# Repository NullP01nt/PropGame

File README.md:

PropGame
========

Documentation, designs and source code for our Propeller-based Game Console.

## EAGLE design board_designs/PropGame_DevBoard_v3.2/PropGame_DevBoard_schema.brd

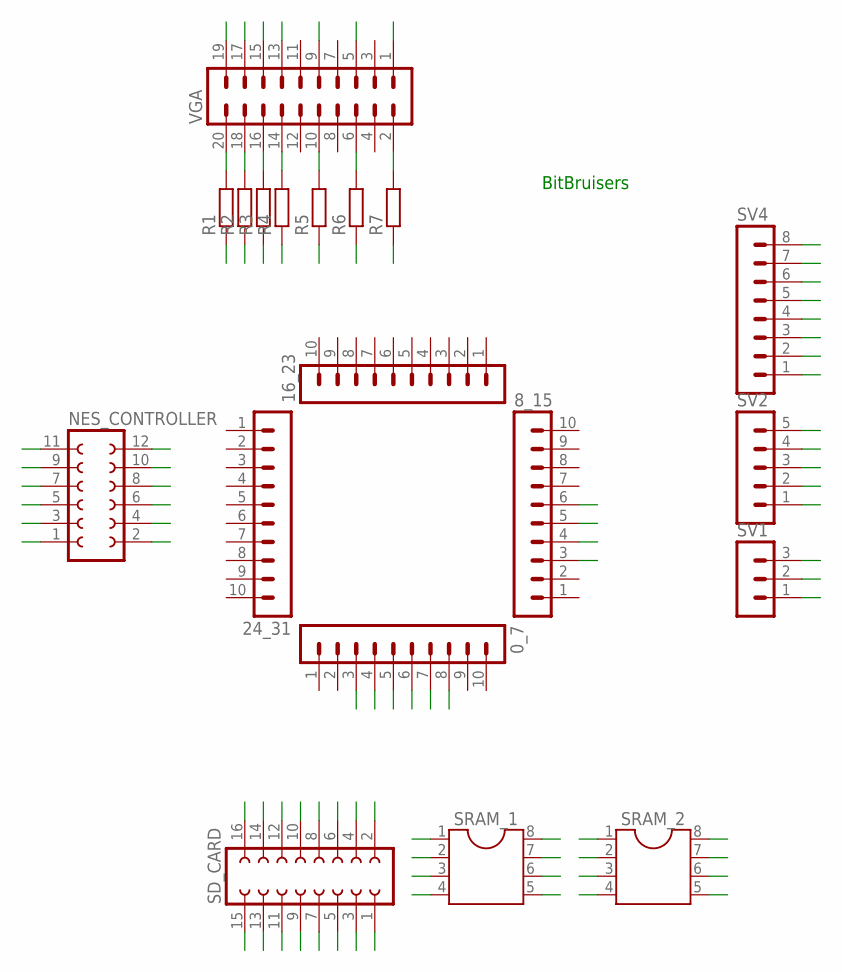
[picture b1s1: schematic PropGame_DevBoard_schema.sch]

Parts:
0_7, 8_15, 16_23, 24_31: MA10-1
NES_CONTROLLER: FE06-2
R1, R2, R3, R4, R5, R6, R7: R-EU_0204/7; 0204/7
SD_CARD: FE08-2
SRAM_1, SRAM_2: DIL8; DIL08
SV1: MA03-1
SV2: MA05-1
SV4: MA08-1
VGA: MA10-2

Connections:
3V3: SD_CARD.13, SD_CARD.14, SRAM_1.8, SRAM_2.8, SV1.1, SV1.2, SV1.3
5V: NES_CONTROLLER.3, NES_CONTROLLER.4, SD_CARD.11, SD_CARD.12, SV4.1, SV4.2, SV4.3
CLK: 8_15.3, NES_CONTROLLER.11, NES_CONTROLLER.12
CS_1: 0_7.6, SD_CARD.9, SD_CARD.10
CS_2: 0_7.7, SRAM_1.1
CS_3: 0_7.8, SRAM_2.1
DATA1: 8_15.5, NES_CONTROLLER.7, NES_CONTROLLER.8
DATA2: 8_15.6, NES_CONTROLLER.5, NES_CONTROLLER.6
GND: NES_CONTROLLER.1, NES_CONTROLLER.2, SD_CARD.1, SD_CARD.2, SD_CARD.15, SD_CARD.16, SRAM_1.4, SRAM_2.4, SV2.1, SV2.2, SV2.3, SV2.4, SV2.5, SV4.4, SV4.5, SV4.6, SV4.7, SV4.8
LATCH: 8_15.4, NES_CONTROLLER.9, NES_CONTROLLER.10
MISO: 0_7.5, SD_CARD.3, SD_CARD.4, SRAM_1.2, SRAM_2.2
MOSI: 0_7.4, SD_CARD.7, SD_CARD.8, SRAM_1.5, SRAM_2.5
unnamed: R1.2, VGA.20
unnamed: R2.2, VGA.18
unnamed: R3.2, VGA.16
unnamed: R4.2, VGA.14
unnamed: R5.2, VGA.10
unnamed: R6.2, VGA.6
unnamed: R7.2, VGA.2
SCK: 0_7.3, SD_CARD.5, SD_CARD.6, SRAM_1.6, SRAM_2.6
W_1: R1.1, VGA.19
W_2: R2.1, VGA.17
W_3: R3.1, VGA.15
W_4: R4.1, VGA.13
W_5: R5.1, VGA.9
W_6: R6.1, VGA.5
W_7: R7.1, VGA.1

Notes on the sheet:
BitBruisers

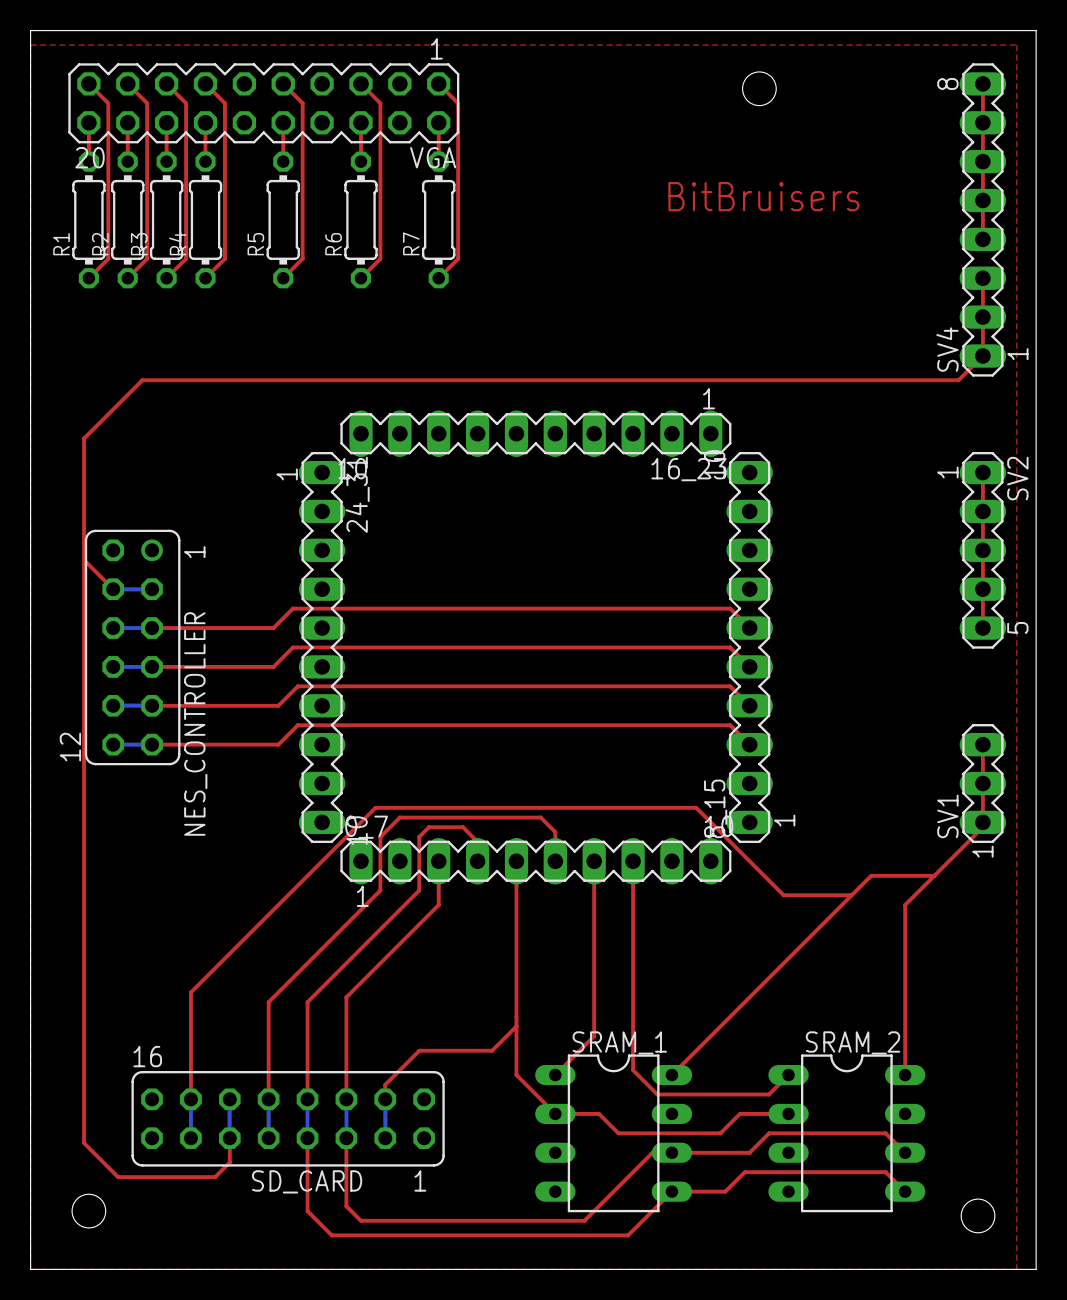
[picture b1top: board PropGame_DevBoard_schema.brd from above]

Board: 2 copper layers, 65.7 x 81.0 mm, 19 parts (0 on the bottom side), 27 nets.

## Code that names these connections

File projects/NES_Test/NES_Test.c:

/**
 * @file NES_Test.c
 * This is the main NES_Test program start point.
 */

/**
 * Main program function.
 */

#include <stdio.h>
#include <stdlib.h>
#include <propeller.h>

// Pin numbers
#define CLOCK   4
#define LATCH   5
#define DATA1   6
#define DATA2   7
#define BITS    8

// Direction types
#define OUTPUT  1
#define INPUT   0

#define HIGH    1
#define LOW     0

// Button values
#define BTN_RIGHT   (1<<7)
#define BTN_LEFT    (1<<6)
#define BTN_DOWN    (1<<5)
#define BTN_UP      (1<<4)
#define BTN_START   (1<<3)
#define BTN_SELECT  (1<<2)
#define BTN_B       (1<<1)
#define BTN_A       (1<<0)

void pinSet(int,int);
unsigned char buttons(void);
void readButtons(void);
int init_gamepad(void);

unsigned char P1_BUTTONS;
unsigned char P2_BUTTONS;

void print_buttons(unsigned char);

int main()
{
    printf("Hello world!\n");
    init_gamepad();
    while(1) {
        readButtons();
        print_buttons(P1_BUTTONS);
        print_buttons(P2_BUTTONS);
/*        if(P1_BUTTONS & BTN_START) {
            printf("[P1] Start pressed!\n");
        } else if(P1_BUTTONS & BTN_SELECT) {
            printf("[P1] Select pressed!\n");
        } else if(P1_BUTTONS & BTN_A) {
            printf("[P1] A pressed!\n");
        } else if(P1_BUTTONS & BTN_B) {
            printf("[P1] B pressed!\n");
        } else if(P1_BUTTONS & BTN_UP) {
            printf("[P1] Up pressed!\n");
        } else if(P1_BUTTONS & BTN_DOWN) {
            printf("[P1] Down pressed!\n");
        } else if(P1_BUTTONS & BTN_LEFT) {
            printf("[P1] Left pressed!\n");
        } else if(P1_BUTTONS & BTN_RIGHT) {
            printf("[P1] Right pressed!\n");
        }

        if(P2_BUTTONS & BTN_START) {
            printf("[P2] Start pressed!\n");
        } else if(P2_BUTTONS & BTN_SELECT) {
            printf("[P2] Select pressed!\n");
        } else if(P2_BUTTONS & BTN_A) {
            printf("[P2] A pressed!\n");
        } else if(P2_BUTTONS & BTN_B) {
            printf("[P2] B pressed!\n");
        } else if(P2_BUTTONS & BTN_UP) {
            printf("[P2] Up pressed!\n");
        } else if(P2_BUTTONS & BTN_DOWN) {
            printf("[P2] Down pressed!\n");
        } else if(P2_BUTTONS & BTN_LEFT) {
            printf("[P2] Left pressed!\n");
        } else if(P2_BUTTONS & BTN_RIGHT) {
            printf("[P2] Right pressed!\n");
        }*/
//        printf("0x%X\n",P1_BUTTONS);
        waitcnt(CLKFREQ/2+CNT);
    }
    return 0;
}

int init_gamepad()
{
    DIRA &= ~((1<<DATA1)|(1<<DATA2));   // DATA1 en DATA2 is INPUT
    DIRA |= ((1<<CLOCK)|(1<<LATCH));    // CLOCK en LATCH is OUTPUT

    pinSet(LATCH, HIGH);
    unsigned char tmp;
    tmp = buttons();
    if (tmp == 0) { return -1;
    }
    printf("%X",tmp);
    return 0;
}

void print_buttons(unsigned char input) {
    int i=BITS;
    printf("RLDUSSBA\n");
    for(i=BITS;i>0;i--) {
        printf("%d",input&(1<<(i-1))?1:0);
    }
    printf("\n");
}

void readButtons() {
    int i=0;
    pinSet(LATCH,LOW);
    pinSet(CLOCK,LOW);
    uint8_t p1b=0,p2b=0;
    uint8_t i1=0,i2=0;
    for(i=BITS;i>0;i--) {
        i1 = (INA & (1<<DATA1)) ? 0 : 1;
        i2 = (INA & (1<<DATA2)) ? 0 : 1;
        p1b |= (i1<<(BITS-i));
        p2b |= (i2<<(BITS-i));
        pinSet(CLOCK,HIGH);
        waitcnt(500+CNT);
        pinSet(CLOCK,LOW);
    }
    P1_BUTTONS = p1b;
    P2_BUTTONS = p2b;
}

unsigned char buttons()
{
    int i=0;
    pinSet(LATCH, LOW);
    pinSet(CLOCK, LOW);
    unsigned char btns = 0;
    unsigned char InBit1 = 0;
    for (i = BITS; i > 0; i--) {
        InBit1 = (INA & (1<<DATA1)) ? 0 : 1;
        btns |= (InBit1<<(BITS-i));
        pinSet(CLOCK,HIGH);
        waitcnt(500+CNT);
        pinSet(CLOCK,LOW);
    }
    pinSet(LATCH,HIGH);
    return btns;
}

void pinSet(int pin, int value)
{
    uint32_t mask = 1 << pin;
    uint32_t data = (value & 1) << pin;
    OUTA = (OUTA & ~mask) | data;
}

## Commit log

2012-11-04 Added documentation URLs for the Propeller and Wii Classic controller
2012-11-04 Added a list for proposed games
2012-11-06 Added an SD Card tutorial for Propeller (In Spin, mind you)
2012-11-06 Added Protoboard documents
2012-11-06 Added SD pinout, renamed the Prop docs
2012-11-06 Added more documents
2012-11-06 Added some new urls, as well as a reference to a SD card lib
2012-11-17 Nice Propeller Cookbook.
2012-11-17 Added link to awesome webshop
2012-11-17 Added documentation regarding external SRAM for the Propeller
2012-11-18 Added a small list of things to get at Farnell as well as specs regarding FAT filesystems
2012-11-19 Added rudimentary partition table reading etc.
2012-11-19 Revised main.c in src/fat/
2012-11-19 Revised partition table stuff again
2012-11-19 Revised main.c and disk.c
2012-11-19 Fixed up main.c so we can load partition entries in a for loop
2012-11-19 Made output as given by the software a bit more readable
2012-11-20 Removed unused imports
2012-11-20 Revised Makefile, added clean as a 'phony' target
2012-11-20 Renamed 'fat' to 'disk' since it encompasses more than just the filesystem
2012-11-20 Started work on FAT interpretation, both FAT16 and FAT32?
2012-11-20 worked on output of dump_ebpb()
2012-11-20 Volume Record is now being properly read, from what I can tell
2012-11-20 Added the USE_FAT32 define again
2012-11-24 Removed disk files, added everything to fat.h and fat.c
2012-11-24 Revised naming for functions, structs etc.
2012-11-25 Revised gitignore to ignore *.swp files
2012-11-25 updated functions to new naming
2012-11-25 Added ignore rules for *.vim files (among others Sessions etc.)
2012-11-25 Seperated FAT16 and FAT32 code
2012-11-25 Fixed signed-ness issue with print_char_bytes
2012-11-25 Changed default file in main.c
2012-11-25 Added example code
2012-11-25 Re-indented example code in docs/FAT32
2012-11-30 Removed old FAT specs document, added new HTML based version. Revised FAT code
2012-12-16 Added blank files for various interfaces
2012-12-16 Added link to Eclipse plugin for PropGCC
2012-12-17 Files for testing with SPI
2012-12-17 Added documentation about SPI for the propeller
2012-12-17 modified files
2013-01-18 Added NES Gamepad project
2013-01-18 Begin NES controller
2013-01-18 Revised Gamepad code
2013-01-18 Added a board configuration stump, have to look at the cache driver
2013-01-18 Added several working folders
2013-01-20 Added full propgcc tar.gz for reference and demos
2013-01-21 Added sd loader stub
2013-01-21 Added Eagle files as well as VGA
2013-01-22 Working on revised makefile, removed sd_cache_loader.c in favour of sd_loader.c
2013-01-22 Added documentation and vgademo
2013-01-22 Added basics for a 'game' project in src/pad_tester
2013-01-22 Added begin for testgame
2013-01-22 Completed gamepad functions, added some pin functions
2013-01-22 Removed built binary files
2013-01-22 Some minor changes, add's and removes
2013-01-22 pad_tester project compiles with Makefile
2013-01-22 revised gamepad.c to allow for SinglePlayer and MultiPlayer definitions
2013-01-22 Removed some stuff, useless
2013-01-22 tags
2013-01-22 Reduced NesGamepad_2 to NesGamepad
2013-01-22 Renamed NesGamepad_2{.c|.side} to NesGamepad{.c|.side}
2013-01-22 added second demo
2013-01-22 Added an include to gamepad.c for standard data sizes
2013-01-22 Added a run target to pad_tester's Makefile
2013-01-23 Started work on segloader, moved gameblade.cfg to pad_tester/
2013-01-23 Added board design and begin snake game
2013-01-23 Added a run target for segloader, modified file I/O slightly, filtering by extension is possible
2013-01-23 Cleaned up the repository
2013-01-23 Added the board config and gamepad code to the segloader directory
2013-01-23 Added doc about VGA and new project for incl vga and game
2013-01-23 Added some more things related to the gamepad code, I missed pins.{c|h} and a reference to PAD_ONE
2013-01-23 Another doc about VGA, this one for the propeller
2013-01-23 Revised vgademo, added a run target to the Makefile, added the board config to the directory, removed a pre-built binary
2013-01-23 Attempt to integrate VGA into SegLoader, non-funct
2013-01-23 Removed all VGA code from SegLoader
2013-01-23 Added common base for makefiles, added text mode VGA to SegLoader, which seems to work
2013-01-23 Revised gitignore so it doesn't list elf files or out files
2013-01-23 Working on SegLoader, has rudimentary controller working
2013-01-23 New board design and added projects for game
2013-01-23 Revised File I/O, it makes an array of 24 file entries and displays them usin VGAText
2013-01-23 Loader menu working like I want to, now off to loader functionality
2013-01-23 Added VGA code for rock_paper_scissors
2013-01-23 Removed hard-coded base pin in segloader.c, now instead you can change pins.h
2013-01-23 Fixed a boo-boo in segloader.c
2013-01-23 Revised common makefile, the gameblade.cfg file now resides with it as a common resource
2013-01-24 Added Rock, Paper & Scissor game
2013-01-24 Optimized game and added some error handling
2013-01-24 Some minor changes, removed dubble stuff
2013-01-24 Revised segloader control scheme, trailing is also fixed
2013-01-24 SegLoader now breaks the while loop when 'selecting' a file
2013-01-24 Added folders for report and presentation
2013-01-24 Renamed and moved several Propeller documentation files
2013-01-24 Revised gitignore so TeX files will not all be uploaded, only *.pdf and *.tex are uploaded
2013-01-24 Added begin workinghours
2013-01-24 Revised presentation
2013-01-24 Revised gitignore, revised common Makefile, added a Makefile to rock_paper_scissors, removed compiled binaries, branched sd_loader to seg_sdloader
2013-01-24 Urenverantwoording zo goed als af
2013-01-24 Removed temporary office file
2013-01-24 Revised gitignore to ignore temporary LibreOffice files
2013-01-24 Urenverantwoording in pdf
2013-01-24 Removed useless files, revised gitignore, added documentation
2013-01-24 deleted seg_sdloader, opting for tertiary stage
2013-01-24 Added docs
2013-01-24 More docs and pictures
2013-01-25 Modified presentation and added notes
2013-01-25 Added loadmenu, a loader based on the SD cache loader
2013-01-25 Added and modified documentation
2013-01-25 Finished SD Loader
2013-01-25 Cleaned up my working directory, 'satisfied' with the loader...
2013-01-25 Added files to the deliverables folder
2013-01-25 Renamed audit deliverables folder
2013-01-28 Revised pins.h, relocated the controller pins
2013-05-16 Revised pins.h in some projects to allow player two port to act for player one in code, added documentation etc.
